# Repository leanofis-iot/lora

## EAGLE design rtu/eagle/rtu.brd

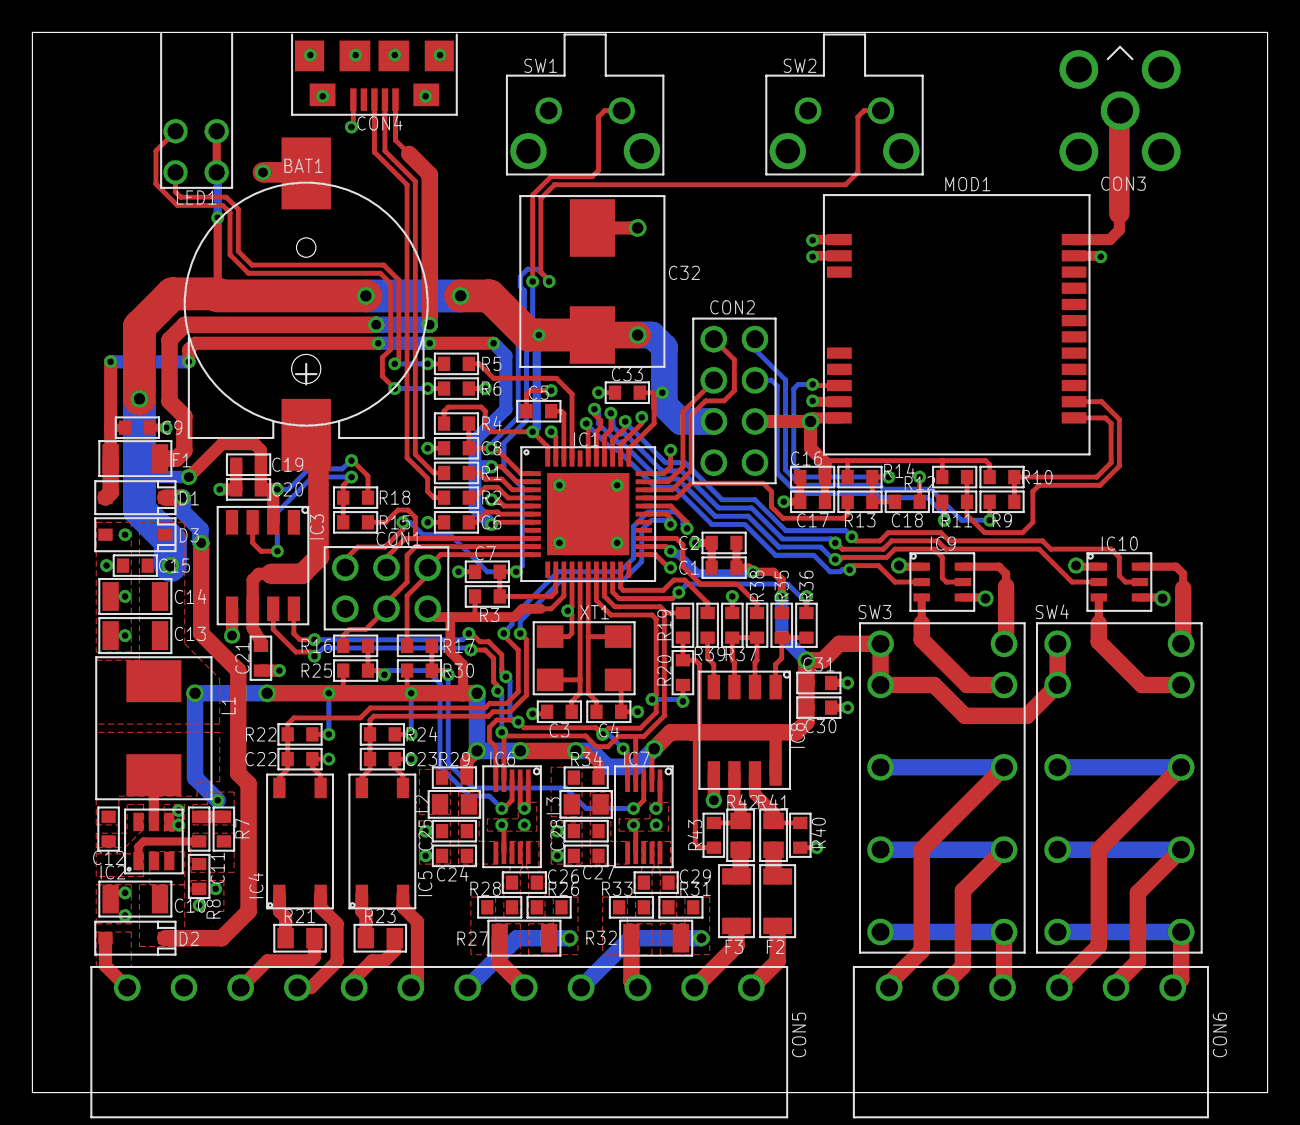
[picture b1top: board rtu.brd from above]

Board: 2 copper layers, 76.2 x 65.4 mm, 109 parts (0 on the bottom side), 87 nets.

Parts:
BAT1: BAT-1220-BC501SM
C1, C2, C3, C4, C5, C6, C7, C8, C9, C11, C12, C15, C16, C17, C18, C19, C20, C21, C22, C23, C24, C25, C26, C27, C28, C29, C30, C31, C33: 0603
C10, C13, C14: 1206
C32: CAPACITOR-SMD-8
CON1: ISP
CON2: HEADER-8P-2R-DIP-2_54MM
CON3: SMA-RF
CON4: USB-MICRO-B-SMD
CON5: KF2EDGR-3.5-12P
CON6: KF2EDGR-3.5-6P
D1, D2, D3: SOD123-DIODE
F1, F2, F3: 1206
IC1: QFN-44
IC2: SOT23-6
IC3, IC8: SOIC-8
IC4, IC5: OPTO-SMD
IC6, IC7: VSSOP-10
IC9, IC10: SC74-6
L1: INDUCTOR-0520-0630
L2, L3: 0805
LED1: LED-HOLDER-2P
MOD1: RAK4200
R1, R2, R3, R4, R5, R6, R7, R8, R9, R10, R11, R12, R13, R14, R15, R16, R17, R18, R19, R20, R22, R24, R25, R26, R28, R29, R30, R31, R33, R34, R35, R36, R37, R38, R39, R40, R43: 0603
R21, R23, R41, R42: 0805
R27, R32: 1206
SW1, SW2: B3F-3150-52-55
SW3, SW4: HFD2-L2
XT1: CRYSTAL-5032-4P

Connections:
GND: BAT1.-, C1.1, C2.1, C3.1, C4.1, C5.1, C6.1, C7.1, C8.2, C9.1, C10.1, C13.1, C14.1, C15.1, C16.1, C17.1, C18.1, C19.1, C20.1, C21.1, C22.1, C23.1, C24.1, C25.1, C27.1, C28.1, C30.1, C31.1, C32.1, C33.1, CON1.6, CON2.4, CON2.8, CON3.2, CON3.3, CON3.4, CON3.5, CON4.5, CON4.6, CON4.7, CON4.8, CON4.9, CON4.10, CON4.11, CON5.11, D3.2, IC1.5, IC1.15, IC1.23, IC1.33, IC1.35, IC1.43, IC1.45, IC2.4, IC3.5, IC4.3, IC5.3, IC6.1, IC6.2, IC6.7, IC7.1, IC7.7, IC8.5, IC9.1, IC9.4, IC10.1, IC10.4, MOD1.11, MOD1.13, MOD1.14, MOD1.19, R6.1, R8.1, R37.1, R40.1, SW1.2, SW1.3, SW1.4, SW2.2, SW2.3, SW2.4, XT1.2, XT1.4
unnamed: IC1.41, R5.1
unnamed: C18.2, MOD1.18, R13.1, R14.1
unnamed: CON1.1, IC1.11, R17.2
unnamed: CON3.1, MOD1.12
unnamed: CON2.2, IC1.32
unnamed: MOD1.1, R9.2, R10.1
unnamed: MOD1.2, R11.2, R12.1
unnamed: LED1.1, R6.2
unnamed: CON1.4, IC1.10, R16.2
unnamed: C3.2, IC1.16, XT1.1
unnamed: CON2.1, IC1.31
unnamed: C4.2, IC1.17, XT1.3
unnamed: C16.2, C17.2, CON2.7, MOD1.20, R10.2, R12.2, R14.2
unnamed: CON2.5, R9.1
unnamed: LED1.3, R5.2
unnamed: CON2.6, R11.1
unnamed: C29.1, IC7.8, IC7.9, R33.2
unnamed: CON4.2, R1.1
unnamed: CON4.3, R2.1
unnamed: IC4.1, R21.2
unnamed: C29.2, IC7.10, R31.2
unnamed: IC1.30, R13.2
unnamed: IC6.3, R16.1, R25.2
unnamed: IC1.36, IC10.5
unnamed: IC7.3, R17.1, R30.2
unnamed: IC9.6, SW3.L1-
unnamed: L3.1, R34.2
unnamed: IC9.3, SW3.L2-
unnamed: C8.1, IC1.1, R4.1, SW2.1
unnamed: CON5.4, R31.1, R32.1
unnamed: C5.2, IC1.42
unnamed: C23.2, IC1.28, IC5.4, R24.2
unnamed: IC5.1, R23.2
unnamed: C6.2, IC1.6
unnamed: C22.2, IC1.29, IC4.4, R22.2
unnamed: IC1.37, IC10.2
unnamed: CON6.1, SW4.NO1, SW4.NO2
unnamed: CON5.3, R32.2, R33.1
unnamed: C7.2, CON1.5, IC1.13, R3.2, SW1.1
unnamed: C27.2, C28.2, IC7.6, L3.2
unnamed: IC1.3, R1.2
unnamed: IC1.4, R2.2
unnamed: CON1.3, IC1.9, R15.2
unnamed: CON5.2, F3.1
unnamed: IC8.1, R35.2, R36.2
unnamed: IC8.4, R39.2
unnamed: CON5.7, IC5.2
unnamed: CON5.9, IC4.2
unnamed: IC8.7, R40.2, R41.2
unnamed: IC8.6, R42.2, R43.2
unnamed: IC8.2, IC8.3, R37.2, R38.2
unnamed: F3.2, R42.1
unnamed: CON5.8, R23.1
unnamed: CON4.1, F1.1
unnamed: C10.2, D1.1, D2.1, IC2.2, IC2.3
unnamed: BAT1.+, C21.2, IC3.6
unnamed: CON5.6, R26.2, R27.2
unnamed: CON5.1, F2.1
unnamed: IC1.20, R36.1
unnamed: IC1.21, R39.1
unnamed: IC1.25, R38.1
unnamed: IC10.6, SW4.L1-
unnamed: C12.2, IC2.6
unnamed: C12.1, IC2.5, L1.2
unnamed: CON6.2, SW4.NC1, SW4.NC2
unnamed: C26.2, IC6.10, R26.1
unnamed: C26.1, IC6.8, IC6.9, R28.1
unnamed: IC3.3, R15.1, R18.2
unnamed: L2.1, R29.2
unnamed: C11.1, IC2.1, R7.2, R8.2
unnamed: IC1.18, IC3.8, IC6.5, IC7.5, R20.2
unnamed: CON6.3, SW4.C1, SW4.C2
unnamed: C24.2, C25.2, IC6.6, L2.2
unnamed: IC1.19, IC3.7, IC6.4, IC7.4, R19.2
unnamed: F2.2, R41.1
unnamed: CON5.5, R27.1, R28.2
unnamed: IC10.3, SW4.L2-
unnamed: CON5.10, R21.1
unnamed: CON6.4, SW3.NO1, SW3.NO2
unnamed: CON6.5, SW3.NC1, SW3.NC2
unnamed: CON6.6, SW3.C1, SW3.C2
unnamed: IC1.38, IC9.5
unnamed: IC1.39, IC9.2
UVCC: C9.2, D1.2, F1.2, IC1.2, IC1.7
VCC: C1.2, C2.2, C11.2, C13.2, C14.2, C15.2, C19.2, C20.2, C30.2, C31.2, C32.2, C33.2, CON1.2, CON2.3, D3.1, IC1.14, IC1.24, IC1.34, IC1.44, IC3.2, IC7.2, IC8.8, L1.1, LED1.2, LED1.4, R3.1, R4.2, R7.1, R18.1, R19.1, R20.1, R22.1, R24.1, R25.1, R29.1, R30.1, R34.1, R35.1, R43.1, SW3.L1+, SW3.L2+, SW4.L1+, SW4.L2+
VEXT: CON5.12, D2.2

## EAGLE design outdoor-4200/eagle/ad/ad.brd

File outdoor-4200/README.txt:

SWAP DIGITAL PINNS 3,2 TO 0,1
USE PULLUPS FOR SCL,SDA
DIGITAL PINS TO MOST RIGHT OF CONNECTOR
EDIT ATTACHINTERRUPT
----------------------------------------------------------------------------
HWB 10K GND
CONF CALIBRATE
2MM FULL JUMPER RESISTOR

---------------------------
CONNECTORS
C1,2,3,4,5,6,8
XT1
R2,3,4
LED1
SW1

LoRaWAN Class A/C, EU868MHz
Periodical and Alarm Uplink 
Full Configuration via USB / downlink
Over The Air Activation OTAA
Plug & Play The Things Network, Cayenne

2 Channel Analog Inputs
2 Single / 2 Differential, 0-5V / 0-10V / 4-20ma 
2 Channel Digital Inputs
Logic / Dry Contact / Pulse Counter
Over Voltage, ESD Protection

3.6V Battery, C size,  9Ah, up to 10 years
Managable Power Output 3.3V / 5V 
External Power Input

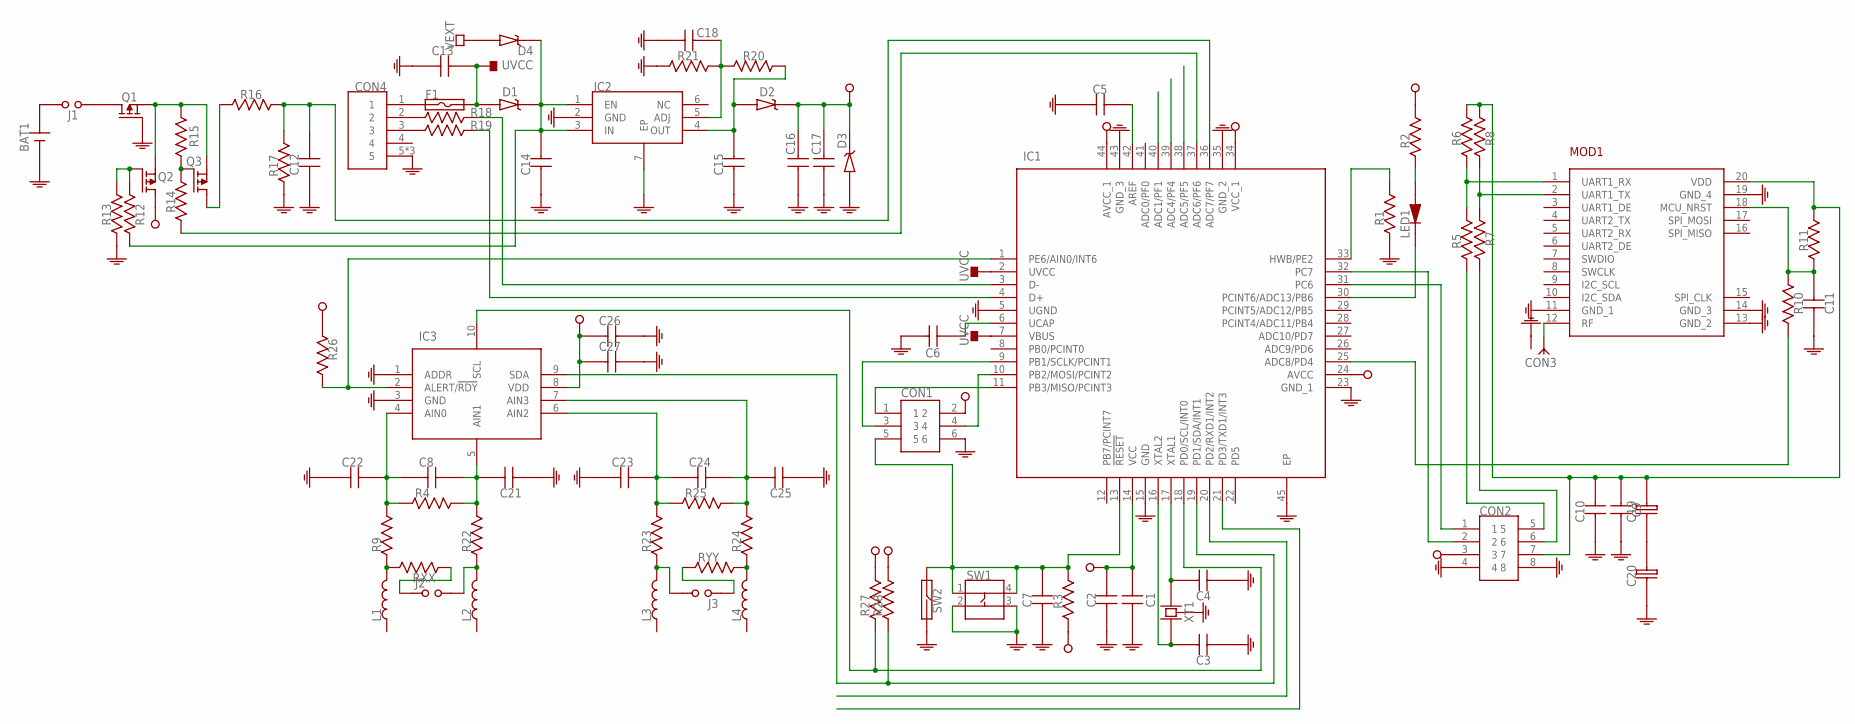
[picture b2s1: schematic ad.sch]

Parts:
BAT1: 211P-C-HOLDER
C1, C2, C3, C4, C5, C6, C7, C8, C9, C10, C11, C12, C13, C16, C17, C18, C21, C22, C23, C24, C25, C26, C27: CAPACITOR-0603; 0603
C14, C15: CAPACITOR-0805; 0805
C19, C20: CAPACITOR-8-3.5
CON1: ISP
CON2: HEADER-8P-2R-DIP-2_54MM
CON3: SMA-RF
CON4: USB-MICRO-DIP-VER
D1, D2, D4: DIODE-SCHOTTKY; SOD123-DIODE
D3: ZENER-SOD123; SOD123-DIODE
F1: FUSE-1206; 1206
IC1: ATMEGA32U4-MU; QFN-44
IC2: MIC5219-ADJ-TDFN-6; TDFN-6
IC3: ADS1115IRUGT; X2QFN-10
J1, J2, J3: JUMPER; HEADER-2P-DIP-2_54MM
L1, L2, L3, L4: INDUCTOR-0805; 0805
LED1: LED-0805; 0805-LED
MOD1: RAK4200
Q1, Q2, Q3: P-MOSFET; SOT23-3
R1, R2, R3, R5, R6, R7, R8, R10, R11, R12, R13, R14, R15, R16, R17, R18, R19, R20, R21, R26, R27, R28: RESISTOR-0603; 0603
R4, R9, R22, R23, R24, R25: RESISTOR-0805; 0805
RXX: RESISTOR-1206; 1206
RYY: RESISTOR-1206; 1206
SW1: BUTTON-4P-SMD-5X5
SW2: REED-DIP
XT1: CRYSTAL-5032-4P

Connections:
GND: BAT1.2 (-), C1.1, C2.1, C3.1, C4.1, C5.1, C6.1, C7.1, C9.1, C10.1, C11.1, C12.1, C13.1, C14.1, C15.1, C16.1, C17.1, C18.1, C20.P$1 (1), C21.1, C22.1, C23.1, C25.1, C26.2, C27.2, CON1.6, CON2.4, CON2.8, CON3.2 (GND), CON3.3 (GND), CON3.4 (GND), CON3.5 (GND), CON4.5, CON4.6 (5), CON4.7 (5), D3.2 (A), IC1.5 (UGND), IC1.15 (GND), IC1.23 (GND_1), IC1.35 (GND_2), IC1.43 (GND_3), IC1.45 (EP), IC2.2 (GND), IC2.7 (EP), IC3.1 (ADDR), IC3.3 (GND), MOD1.11 (GND_1), MOD1.13 (GND_2), MOD1.14 (GND_3), MOD1.19 (GND_4), Q1.1 (G), R1.1, R13.1, R17.1, R21.1, SW1.2, SW1.3, SW2.P$2 (2), XT1.2 (GND), XT1.4 (GND)
unnamed: C7.2, CON1.5, IC1.13 (!RESET), R3.2, SW1.1, SW1.4, SW2.P$1 (1)
unnamed: C11.2, MOD1.18 (MCU_NRST), R10.1, R11.1
unnamed: CON1.1, IC1.11 (PB3/MISO/PCINT3)
unnamed: CON3.1 (ANT), MOD1.12 (RF)
unnamed: J1.1, Q1.3 (D)
unnamed: MOD1.1 (UART1_RX), R5.2, R6.1
unnamed: MOD1.2 (UART1_TX), R7.2, R8.1
unnamed: BAT1.1 (+), J1.2 (3)
unnamed: CON1.4, IC1.10 (PB2/MOSI/PCINT2)
unnamed: C3.2, IC1.16 (XTAL2), XT1.1
unnamed: CON2.1, IC1.31 (PC6)
unnamed: C4.2, IC1.17 (XTAL1), XT1.3 (2)
unnamed: C9.2, C10.2, C19.P$2 (2), CON2.7, MOD1.20 (VDD), R6.2, R8.2, R11.2
unnamed: CON2.6, R7.1
unnamed: C18.2, IC2.5 (ADJ), R20.2, R21.2
unnamed: IC1.25 (ADC8/PD4), R10.2
unnamed: IC1.30 (PCINT6/ADC13/PB6), LED1.1 (K)
unnamed: C8.1, C22.2, IC3.4 (AIN0), R4.1, R9.2
unnamed: C19.P$1 (1), C20.P$2 (2)
unnamed: C8.2, C21.2, IC3.5 (AIN1), R4.2, R22.2
unnamed: C23.2, C24.1, IC3.6 (AIN2), R23.2, R25.1
unnamed: C24.2, C25.2, IC3.7 (AIN3), R24.2, R25.2
unnamed: L1.2, R9.1, RXX.2
unnamed: J2.2 (3), L2.2, R22.1
unnamed: J3.2 (3), L3.2, R23.1
unnamed: CON2.2, IC1.32 (PC7)
unnamed: L4.2, R24.1, RYY.2
unnamed: C5.2, IC1.42 (AREF)
unnamed: Q3.1 (G), R14.2, R15.2
unnamed: CON4.1, F1.1
unnamed: C6.2, IC1.6 (UCAP)
unnamed: LED1.2 (A), R2.1
unnamed: C12.2, IC1.36 (ADC7/PF7), R16.2, R17.2
unnamed: IC1.1 (PE6/AIN0/INT6), IC3.2 (ALERT/!RDY), R26.2
unnamed: C14.2, D1.1 (K), D4.1 (K), IC2.1 (EN), IC2.3 (IN), R12.1
unnamed: J2.1, RXX.1
unnamed: C15.2, D2.2 (A), IC2.4 (OUT), R20.1
unnamed: CON4.2, R18.1
unnamed: CON4.3, R19.1
unnamed: IC1.3 (D-), R18.2
unnamed: IC1.4 (D+), R19.2
unnamed: CON1.3, IC1.9 (PB1/SCLK/PCINT1)
unnamed: J3.1, RYY.1
unnamed: IC1.37 (ADC6/PF6), R14.1
unnamed: Q2.1 (G), R12.2, R13.2
unnamed: Q1.2 (S), Q2.2 (S), Q3.2 (S), R15.1
unnamed: Q3.3 (D), R16.1
unnamed: CON2.5, R5.1
unnamed: IC1.33 (HWB/PE2), R1.2
unnamed: IC1.18 (PD0/SCL/INT0), IC3.10 (SCL), R27.1
unnamed: IC1.19 (PD1/SDA/INT1), IC3.9 (SDA), R28.1
UVCC: C13.2, D1.2 (A), F1.2, IC1.2 (UVCC), IC1.7 (VBUS)
VCC: C1.2, C2.2, C16.2, C17.2, C26.1, C27.1, CON1.2, CON2.3, D2.1 (K), D3.1 (K), IC1.14 (VCC), IC1.24 (AVCC), IC1.34 (VCC_1), IC1.44 (AVCC_1), IC3.8 (VDD), Q2.3 (D), R2.2, R3.1, R26.1, R27.2, R28.2
VEXT: D4.2 (A)

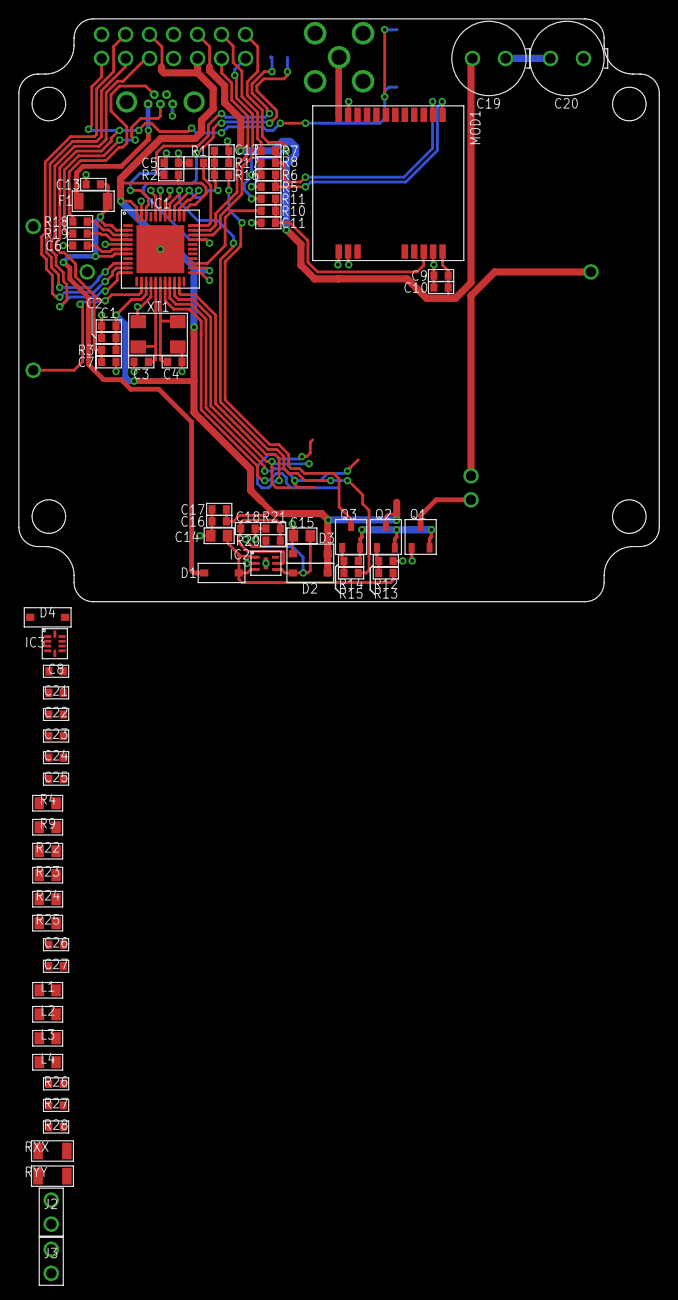
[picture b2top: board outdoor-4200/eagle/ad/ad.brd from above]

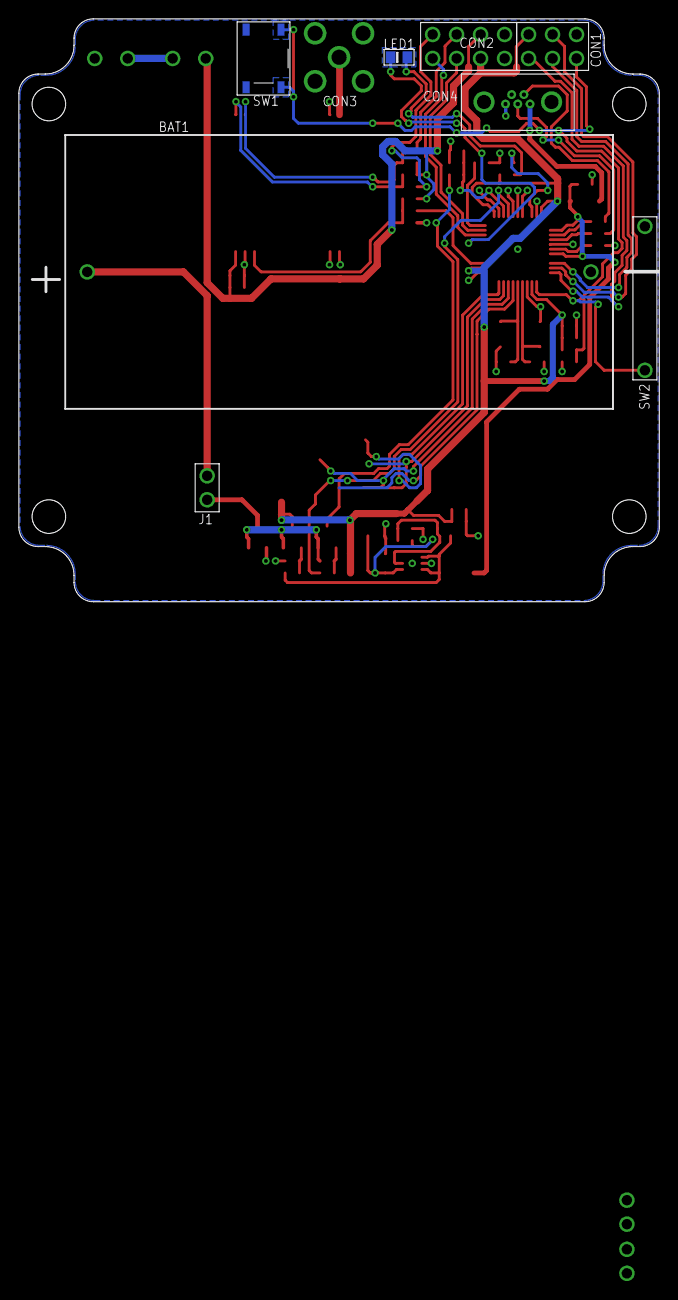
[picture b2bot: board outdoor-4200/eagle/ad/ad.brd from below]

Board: 2 copper layers, 67.8 x 61.7 mm, 85 parts (9 on the bottom side), 54 nets.

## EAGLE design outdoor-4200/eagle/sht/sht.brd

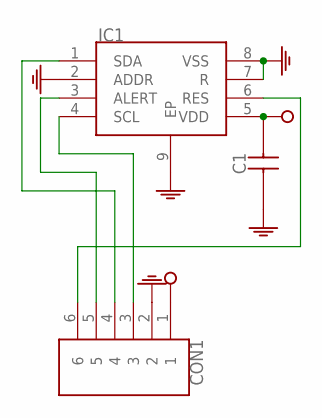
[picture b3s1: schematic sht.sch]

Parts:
C1: CAPACITOR-0603; 0603
CON1: HEADER-6P-DIP-2_54MM
IC1: SHT3X-DIS

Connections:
GND: C1.1, CON1.2, IC1.2 (ADDR), IC1.7 (R), IC1.8 (VSS), IC1.9 (EP)
unnamed: CON1.6, IC1.6 (RES)
unnamed: CON1.4, IC1.1 (SDA)
unnamed: CON1.3, IC1.4 (SCL)
unnamed: CON1.5, IC1.3 (ALERT)
VCC: C1.2, CON1.1, IC1.5 (VDD)

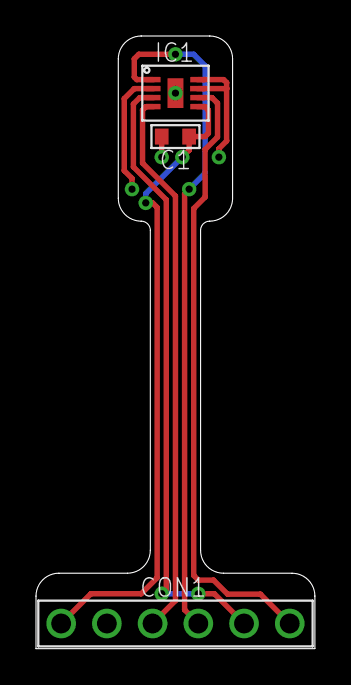
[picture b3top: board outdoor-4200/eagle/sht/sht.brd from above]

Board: 2 copper layers, 15.5 x 34.0 mm, 3 parts (0 on the bottom side), 6 nets.

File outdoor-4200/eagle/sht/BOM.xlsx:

IC1 | 1 | SHT31-DIS-F2.5KS | DFN-8
CON1 | 1 | HEADER 2.54MM 6P | DIP
C1 | 1 | 100NF | 0603

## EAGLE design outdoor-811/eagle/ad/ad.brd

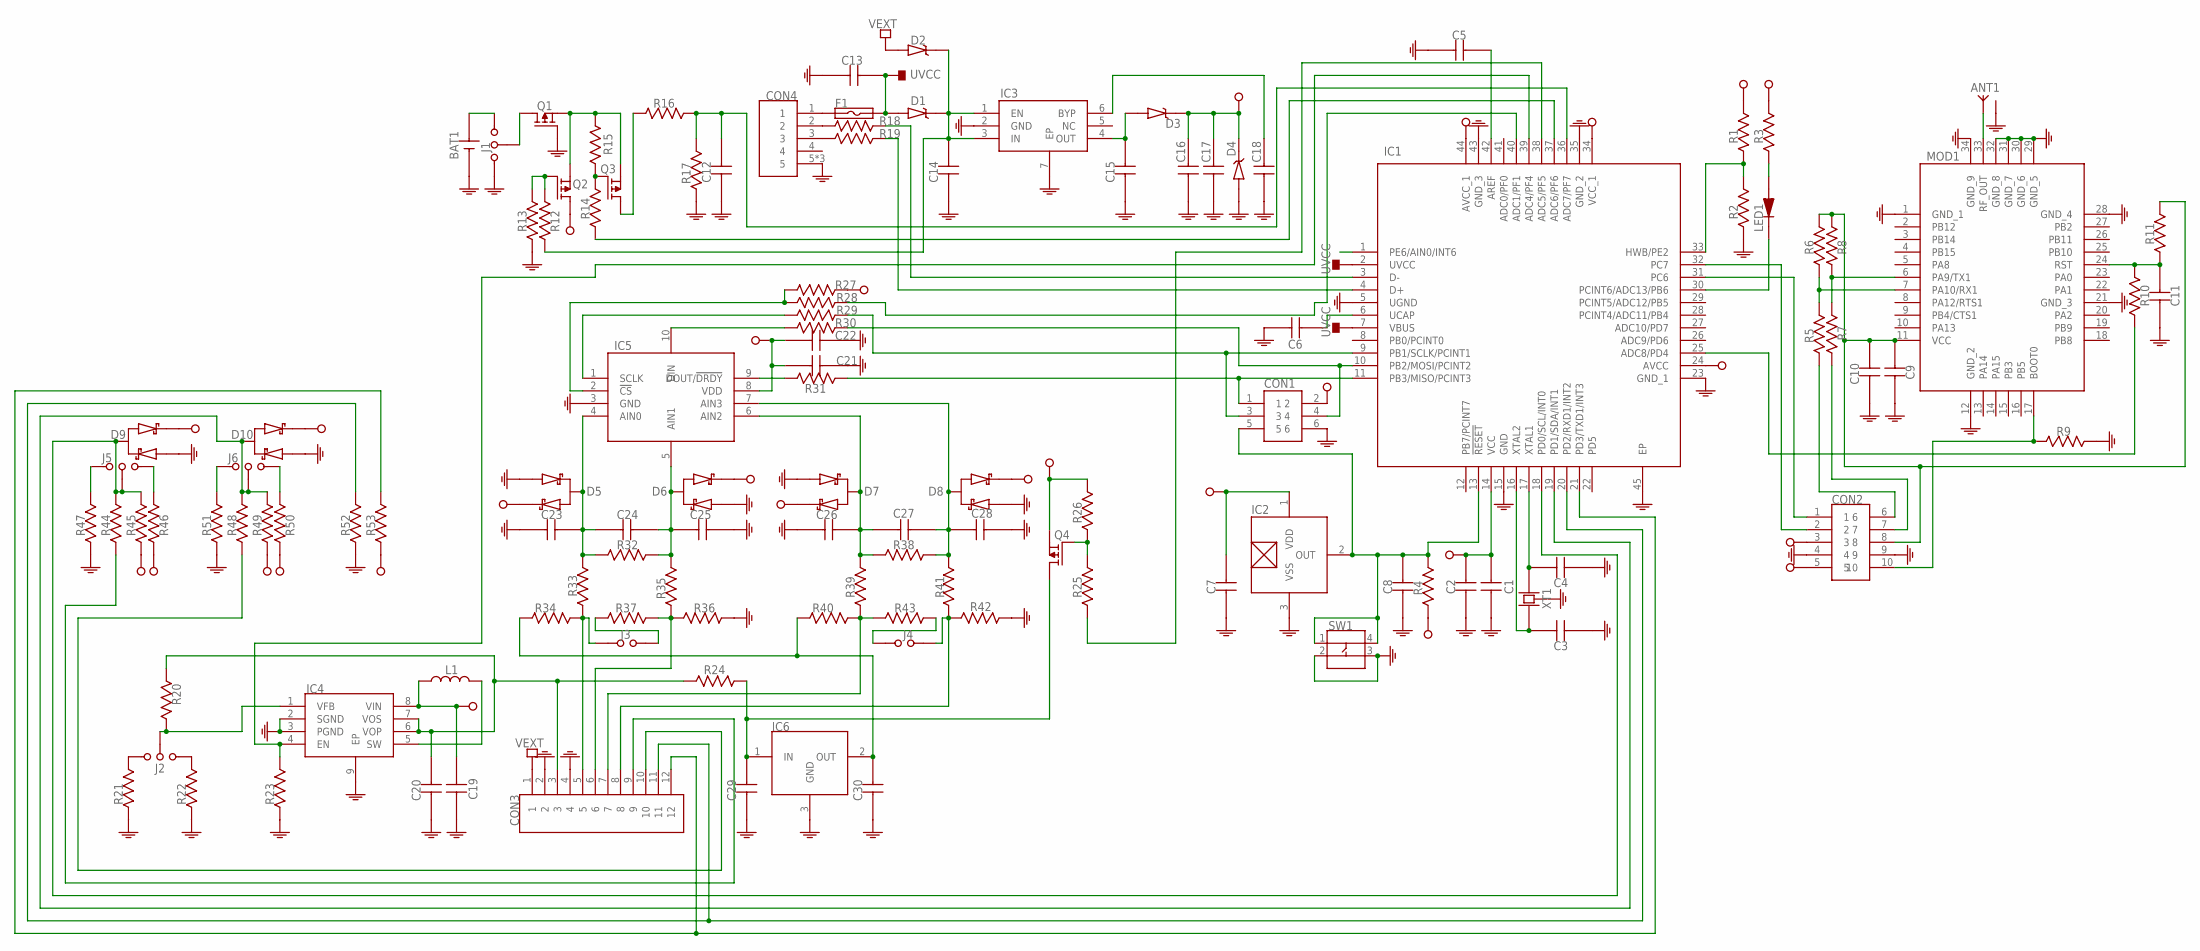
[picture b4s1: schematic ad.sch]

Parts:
ANT1: SMA-RF
BAT1: 211P-C-HOLDER
C1, C2, C3, C4, C5, C6, C7, C8, C9, C10, C11, C12, C13, C16, C17, C18, C21, C22, C23, C24, C25, C26, C27, C28, C29, C30: CAPACITOR-0603; 0603
C14, C15, C19, C20: CAPACITOR-0805; 0805
CON1: ISP
CON2: HEADER-10P-2R-DIP-2_54MM
CON3: CON-12P-2_54MM-141V
CON4: USB-MICRO-DIP-VER
D1, D2, D3: DIODE-SCHOTTKY; SOD123-DIODE
D4: ZENER-SOD123; SOD123-DIODE
D5, D6, D7, D8, D9, D10: SCHOTTKY-SERIE-3P; SOT23-3
F1: FUSE-1206; 1206
IC1: ATMEGA32U4-MU; QFN-44
IC2: S-5712-SOT23-3; SOT23-3
IC3: MIC5219-VDFN-6; VDFN-6
IC4: MCP1640-DFN-8; DFN-8-2X3
IC5: ADS1118IRUGT; X2QFN-10
IC6: VREF-SOT23-3; SOT23-3
J1, J2, J5, J6: JUMPER-3P; HEADER-3P-DIP-2_54MM
J3, J4: JUMPER; HEADER-2P-DIP-2_54MM
L1: INDUCTOR-0520-0630
LED1: LED-0805
MOD1: RAK811
Q1, Q2, Q3, Q4: P-MOSFET; SOT23-3
R1, R2, R3, R4, R5, R6, R7, R8, R9, R10, R11, R12, R13, R14, R15, R16, R17, R18, R19, R20, R21, R22, R23, R24, R25, R26, R27, R28, R29, R30, R31, R45, R49, R52, R53: RESISTOR-0603; 0603
R32, R33, R34, R35, R36, R37, R38, R39, R40, R41, R42, R43, R44, R46, R47, R48, R50, R51: RESISTOR-0805; 0805
SW1: BUTTON-4P-SMD-5X5
XT1: CRYSTAL-5032-4P

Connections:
GND: ANT1.2 (GND), ANT1.3 (GND), ANT1.4 (GND), ANT1.5 (GND), BAT1.2 (-), C1.1, C2.1, C3.1, C4.1, C5.1, C6.1, C7.1, C8.1, C9.1, C10.1, C11.1, C12.1, C13.1, C14.1, C15.1, C16.1, C17.1, C18.1, C19.1, C20.1, C21.1, C22.2, C23.1, C25.2, C26.1, C28.1, C29.1, C30.1, CON1.6, CON2.4, CON2.9, CON3.2, CON3.4, CON4.5, CON4.6 (5), CON4.7 (5), D4.2 (A), D5.1, D6.1, D7.1, D8.1, D9.1, D10.1, IC1.5 (UGND), IC1.15 (GND), IC1.23 (GND_1), IC1.35 (GND_2), IC1.43 (GND_3), IC1.45 (EP), IC2.3 (VSS), IC3.2 (GND), IC3.7 (EP), IC4.2 (SGND), IC4.3 (PGND), IC4.9 (EP), IC5.3 (GND), IC6.3 (GND), J1.1, MOD1.1 (GND_1), MOD1.12 (GND_2), MOD1.21 (GND_3), MOD1.28 (GND_4), MOD1.29 (GND_5), MOD1.30 (GND_6), MOD1.31 (GND_7), MOD1.32 (GND_8), MOD1.34 (GND_9), Q1.1 (G), R2.1, R9.2, R13.1, R17.1, R21.1, R22.1, R23.1, R36.1, R42.1, R47.1, R51.1, R52.1, SW1.2, SW1.3, XT1.2 (GND), XT1.4 (GND)
unnamed: IC5.1 (SCLK), R29.2
unnamed: C11.2, MOD1.24 (RST), R10.1, R11.1
unnamed: CON1.1, IC1.11 (PB3/MISO/PCINT3), R31.2
unnamed: ANT1.1 (ANT), MOD1.33 (RF_OUT)
unnamed: CON3.5, J3.1, R33.1, R34.2
unnamed: MOD1.7 (PA10/RX1), R5.2, R6.1
unnamed: MOD1.6 (PA9/TX1), R7.2, R8.1
unnamed: IC5.2 (!CS), R27.1, R28.2
unnamed: CON1.4, IC1.10 (PB2/MOSI/PCINT2), R30.2
unnamed: C3.2, IC1.16 (XTAL2), XT1.1
unnamed: CON2.1, IC1.31 (PC6)
unnamed: C4.2, IC1.17 (XTAL1), XT1.3 (2)
unnamed: C9.2, C10.2, CON2.8, MOD1.11 (VCC), R6.2, R8.2, R11.2
unnamed: CON2.7, R7.1
unnamed: C20.2, CON3.3, IC4.6 (VOP), IC4.7 (VOS), R20.1, R24.2
unnamed: IC1.25 (ADC8/PD4), R10.2
unnamed: IC5.10 (DIN), R30.1
unnamed: IC5.9 (DOUT/!DRDY), R31.1
unnamed: IC1.30 (PCINT6/ADC13/PB6), LED1.1 (K)
unnamed: CON3.7, R39.1, R40.2, R43.2
unnamed: CON3.6, R35.1, R36.2, R37.2
unnamed: IC4.1 (VFB), J2.2, R20.2
unnamed: C24.2, C25.1, D6.3, IC5.5 (AIN1), R32.2, R35.2
unnamed: C23.2, C24.1, D5.3, IC5.4 (AIN0), R32.1, R33.2
unnamed: CON3.8, J4.1, R41.1, R42.2
unnamed: C26.2, C27.2, D7.3, IC5.6 (AIN2), R38.2, R39.2
unnamed: IC1.40 (ADC1/PF1), R28.1
unnamed: C29.2, IC6.1 (IN), Q4.3 (D), R24.1
unnamed: CON2.2, IC1.32 (PC7)
unnamed: C27.1, C28.2, D8.3, IC5.7 (AIN3), R38.1, R41.2
unnamed: C5.2, IC1.42 (AREF)
unnamed: Q3.1 (G), R14.2, R15.2
unnamed: CON4.1, F1.1
unnamed: C6.2, IC1.6 (UCAP)
unnamed: LED1.2 (A), R3.1
unnamed: C12.2, IC1.36 (ADC7/PF7), R16.2, R17.2
unnamed: C18.2, IC3.6 (BYP)
unnamed: C14.2, D1.1 (K), D2.1 (K), IC3.1 (EN), IC3.3 (IN), R12.1
unnamed: J2.1, R22.2
unnamed: C15.2, D3.2 (A), IC3.4 (OUT)
unnamed: CON4.2, R18.1
unnamed: CON4.3, R19.1
unnamed: IC1.3 (D-), R18.2
unnamed: IC1.4 (D+), R19.2
unnamed: CON1.3, IC1.9 (PB1/SCLK/PCINT1), R29.1
unnamed: Q4.1 (G), R25.2, R26.1
unnamed: IC1.37 (ADC6/PF6), R14.1
unnamed: J1.2, Q1.3 (D)
unnamed: J2.3, R21.2
unnamed: IC1.38 (ADC5/PF5), R25.1
unnamed: BAT1.1 (+), J1.3
unnamed: D9.3, IC1.18 (PD0/SCL/INT0), J5.2, R44.2, R45.2
unnamed: Q2.1 (G), R12.2, R13.2
unnamed: D10.3, IC1.19 (PD1/SDA/INT1), J6.2, R48.2, R49.2
unnamed: CON3.12, IC1.21 (PD3/TXD1/INT3), R53.2
unnamed: C30.2, IC6.2 (OUT), R34.1, R40.1
unnamed: Q1.2 (S), Q2.2 (S), Q3.2 (S), R15.1
unnamed: Q3.3 (D), R16.1
unnamed: CON2.6, R5.1
unnamed: IC1.33 (HWB/PE2), R1.1, R2.2
unnamed: CON2.10, MOD1.17 (BOOT0), R9.1
unnamed: C8.2, CON1.5, IC1.13 (!RESET), IC2.2 (OUT), R4.2, SW1.1, SW1.4
unnamed: IC4.5 (SW), L1.2
unnamed: IC1.39 (ADC4/PF4), IC4.4 (EN), R23.2
unnamed: CON3.11, IC1.20 (PD2/RXD1/INT2), R52.2
unnamed: J4.2 (3), R43.1
unnamed: CON3.10, R48.1
unnamed: J3.2 (3), R37.1
unnamed: CON3.9, R44.1
unnamed: J6.1, R51.2
unnamed: J6.3, R50.2
unnamed: J5.1, R47.2
unnamed: J5.3, R46.2
UVCC: C13.2, D1.2 (A), F1.2, IC1.2 (UVCC), IC1.7 (VBUS)
VCC: C1.2, C2.2, C7.2, C16.2, C17.2, C19.2, C21.2, C22.1, CON1.2, CON2.3, CON2.5, D3.1 (K), D4.1 (K), D5.2, D6.2, D7.2, D8.2, D9.2, D10.2, IC1.14 (VCC), IC1.24 (AVCC), IC1.34 (VCC_1), IC1.44 (AVCC_1), IC2.1 (VDD), IC4.8 (VIN), IC5.8 (VDD), L1.1, Q2.3 (D), Q4.2 (S), R1.2, R3.2, R4.1, R26.2, R27.2, R45.1, R46.1, R49.1, R50.1, R53.1
VEXT: CON3.1, D2.2 (A)

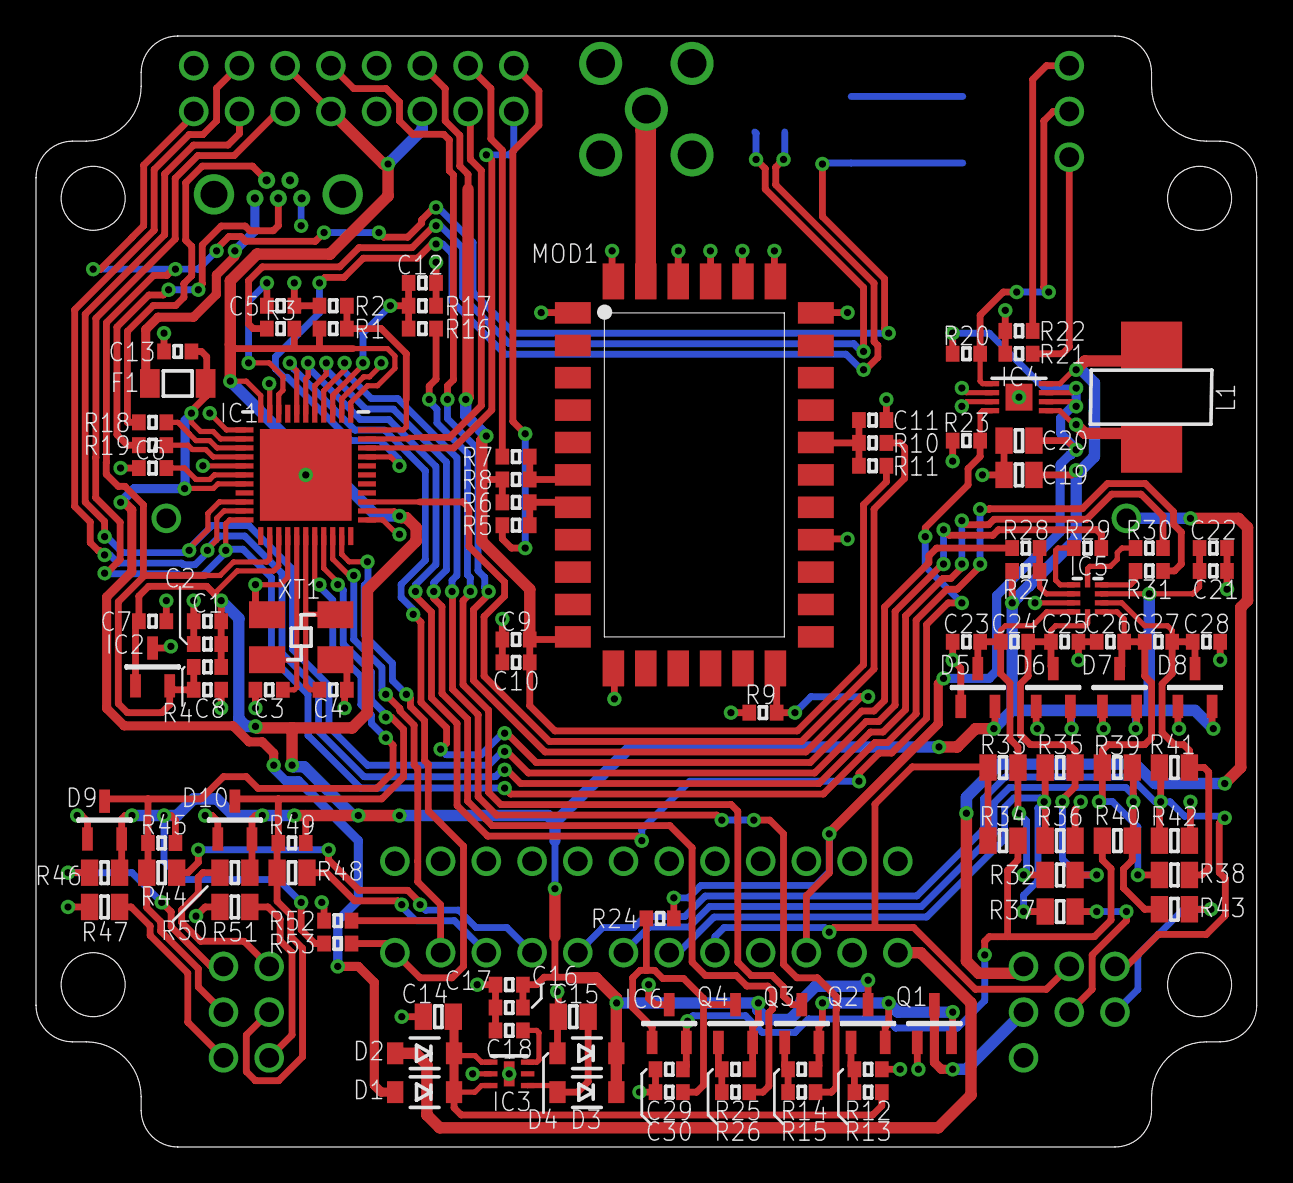
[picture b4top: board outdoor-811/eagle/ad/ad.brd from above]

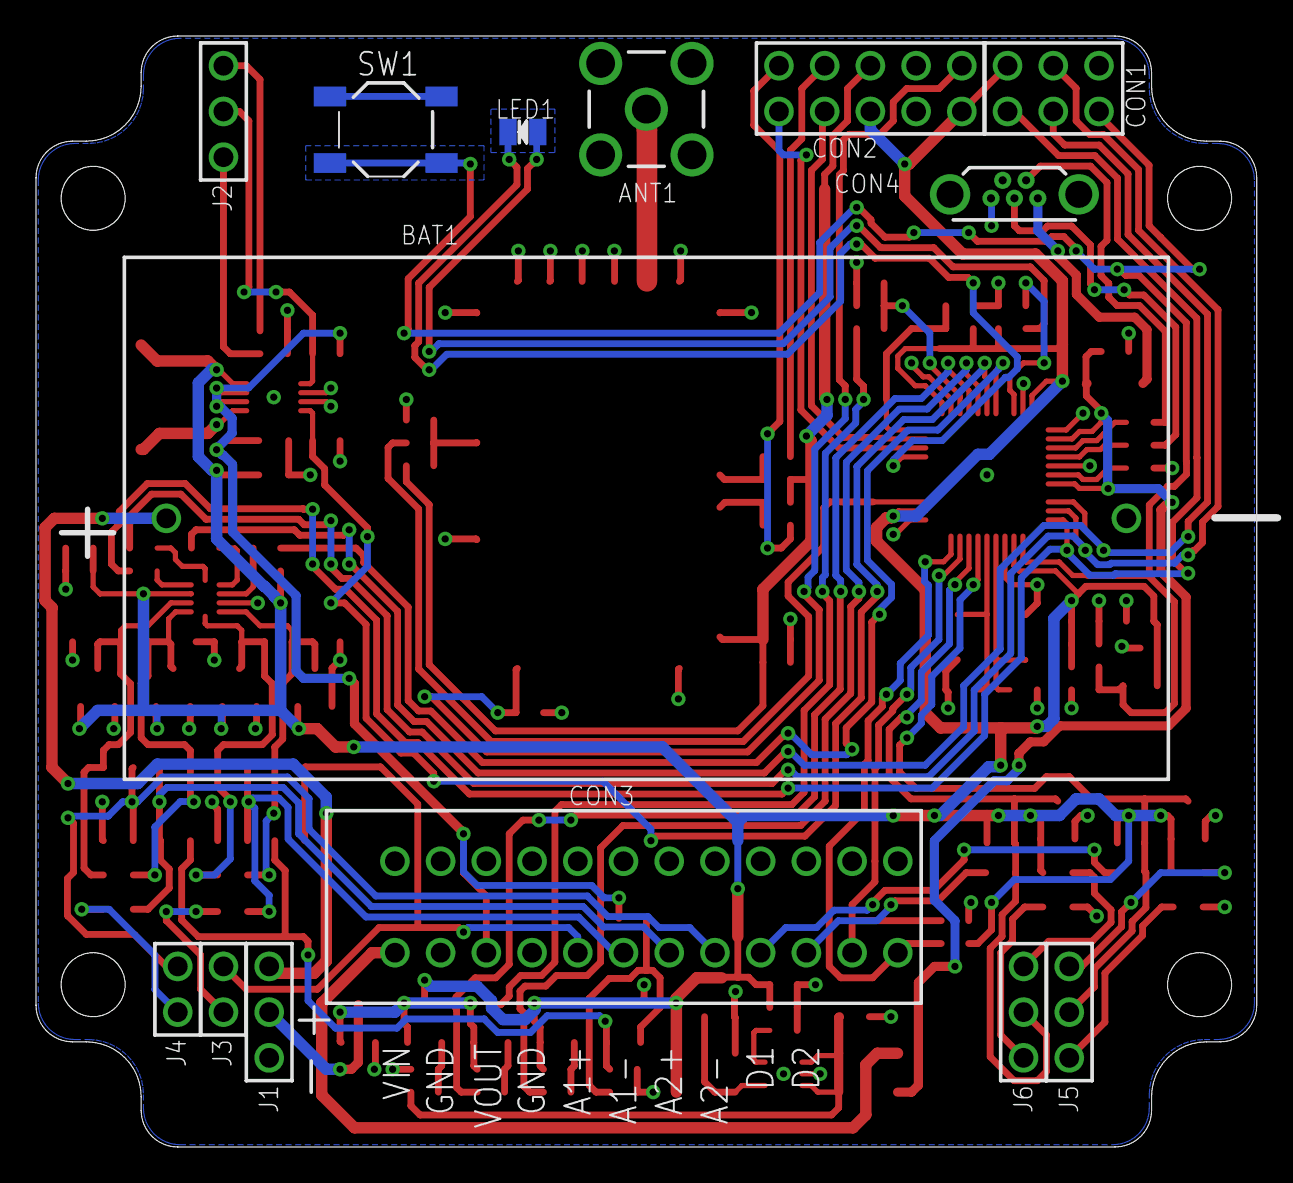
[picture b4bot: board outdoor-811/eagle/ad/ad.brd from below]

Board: 2 copper layers, 67.8 x 61.7 mm, 121 parts (14 on the bottom side), 77 nets.

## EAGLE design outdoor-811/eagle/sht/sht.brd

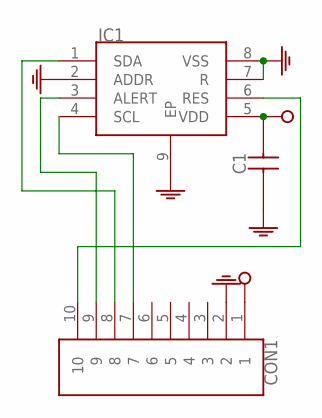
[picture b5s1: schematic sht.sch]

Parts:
C1: CAPACITOR-0603; 0603
CON1: HEADER-10P-DIP-2_54MM
IC1: SHT3X-DIS

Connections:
GND: C1.1, CON1.2, IC1.2 (ADDR), IC1.7 (R), IC1.8 (VSS), IC1.9 (EP)
unnamed: CON1.10, IC1.6 (RES)
unnamed: CON1.8, IC1.1 (SDA)
unnamed: CON1.7, IC1.4 (SCL)
unnamed: CON1.9, IC1.3 (ALERT)
VCC: C1.2, CON1.1, IC1.5 (VDD)

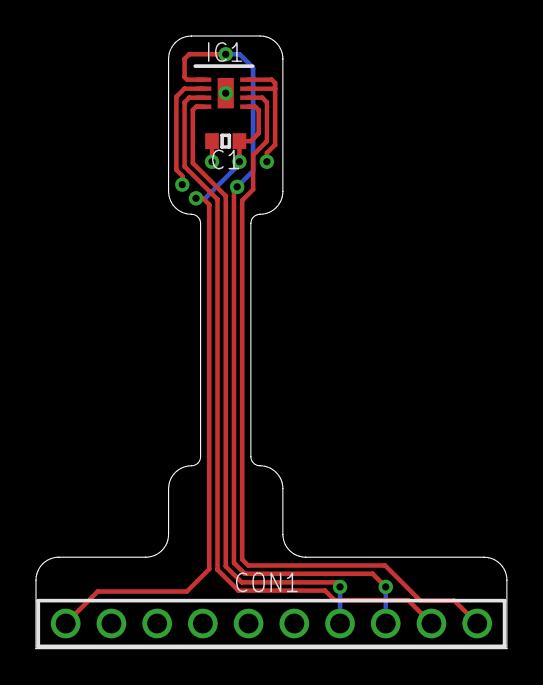
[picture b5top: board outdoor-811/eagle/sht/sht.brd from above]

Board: 2 copper layers, 26.2 x 34.0 mm, 3 parts (0 on the bottom side), 6 nets.

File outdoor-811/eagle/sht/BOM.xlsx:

IC1 | SHT31-DIS | DFN-8
CON1 | HEADER 2.54MM 8P | DIP
C1 | 100NF | 0603
PCB

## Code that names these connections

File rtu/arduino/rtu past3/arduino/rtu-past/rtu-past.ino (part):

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#include <DS3232RTC.h>
#include <WebUSB.h>

const uint8_t BUTTON_PIN        = 7;                // PE6/AIN0/INT6
const uint8_t DS_INT_PIN        = SCK;              // PB1/SCLK/PCINT1
const uint8_t INA_ALR_PIN[2]    = {MOSI, MISO};     // PB2/MOSI/PCINT2, PB3/MISO/PCINT3 
const uint8_t ACT_LED_PIN       = 11;               // PB7/PCINT7
const uint8_t RS_DIR_PIN        = 4;                // PD4/ADC8
const uint8_t DIG_PIN[2]        = {9, 8};           // PB5/ADC12/PCINT5, PB4/ADC11/PCINT4
const uint8_t RAK_RES_PIN       = 10;               // PB6/ADC13/PCINT6
const uint8_t RELAY_PIN[4]      = {A3, A2, A1, A0}; // (S)PF4/ADC4, (R)PF5/ADC5, (S)PF6/ADC6, (R)PF7/ADC7 
const uint8_t JOIN_LED_PIN      = A4;               // PF1/ADC1
const uint8_t RANDOM_PIN        = A5;               // PF0/ADC0

// conf.bytes[alrIndex]
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
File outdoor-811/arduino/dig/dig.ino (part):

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#include "ADS1118.h"
#include <SPI.h>

const uint8_t DIG_PIN[2]    = {3, 2}; // PD0/SCL/INT0, PD1/SDA/INT1
const uint8_t RAK_RES_PIN   = 4;   // PD4/ADC8
const uint8_t LED_PIN       = 10;  // PB6/ADC13/PCINT6
const uint8_t BAT_PIN       = A0;  // PF7/ADC7
const uint8_t BAT_EN_PIN    = A1;  // PF6/ADC6
const uint8_t VREF_EN_PIN   = A2;  // PF5/ADC5
const uint8_t VOUT_EN_PIN   = A3;  // PF4/ADC4
const uint8_t ADS_CS_PIN    = A4;  // PF1/ADC1

float In, R, Val[2], BatVolt;
uint8_t hysRegionPrev[2] = {3, 3};
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
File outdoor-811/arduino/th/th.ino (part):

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#include <Wire.h>
#include "ClosedCube_SHT31D.h"

const uint8_t SHT_ALR_PIN   = 0;  // PD2/RXD1/INT2
const uint8_t SHT_RES_PIN   = 1;  // PD3/TXD1/INT3
const uint8_t RAK_RES_PIN   = 4;   // PD4/ADC8
const uint8_t LED_PIN       = 10;  // PB6/ADC13/PCINT6
const uint8_t BAT_PIN       = A0;  // PF7/ADC7
const uint8_t BAT_EN_PIN    = A1;  // PF6/ADC6
const uint8_t VREF_EN_PIN   = A2;  // PF5/ADC5

float BatVolt;
volatile bool isAlarm = false;
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
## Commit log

2019-12-27 init
